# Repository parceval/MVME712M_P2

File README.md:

# MVME712M P2 Adapter Board

An open-source hardware replacement for the **Motorola MVME712M P2 Adapter**.

This board is designed to interface with Motorola VME CPU modules (such as the MVME147, MVME162, MVME167, and MVME177 series) to provide the necessary signals for the **MVME712M Transition Module**.

## Overview

The MVME712M P2 Adapter is a small passive board that plugs directly into the **P2 connector** on the VME backplane behind the CPU module. It breaks out the SCSI, Serial, and Centronics signals to a 50-pin header (or specific cable) that then connects to the MVME712M bulkhead/transition module.

This repository contains the KiCad design files to manufacture a modern replacement for the original Motorola part, which is often difficult to find or expensive on the used market.

## Hardware Features

* **Form Factor:** Standard VME P2 adapter dimensions.
* **Connectors:** * 96-pin DIN 41612 (Connector for VME P2 backplane).
* High-density or IDC headers for connection to the MVME712M transition board.

* **Compatibility:** Designed for use with Motorola MVME modules and the MVME712 series transition boards.
* **Passive Design:** No active components required; uses direct signal routing according to original Motorola specifications.

## Project Structure

```text
├── gerber/    # Gerbers, Drill files
└── docs/      # Pinout diagrams and reference manuals

```

## Compatibility List

This adapter is typically required for the following Motorola CPU boards when using an MVME712M transition module:

* MVME147
* MVME162 / MVME162P
* MVME167
* MVME172
* MVME177

## Usage

1. **Fabrication:** Use the provided Gerber files in the `Manufacturing/` folder to order PCBs (standard 1.6mm FR4, 1oz copper is sufficient).
2. **Assembly:** Solder the 96-pin DIN 41612 connector (Female/Socket) and the appropriate shrouded headers.
3. **Installation:** * Power down the VME chassis.
* Plug the adapter onto the **P2 pins** on the back of the backplane, directly behind your CPU module.
* Connect the internal ribbon cable from the adapter to your MVME712M transition module.

## License

This project is released under the [CERN Open Hardware Licence](https://cern-ohl.web.cern.ch/)

## Disclaimer

This is a community-driven project. While every effort has been made to ensure accuracy based on original documentation, use this hardware at your own risk. The author is not responsible for any damage to vintage VME equipment.

---

*Created by [parceval*](https://github.com/parceval)

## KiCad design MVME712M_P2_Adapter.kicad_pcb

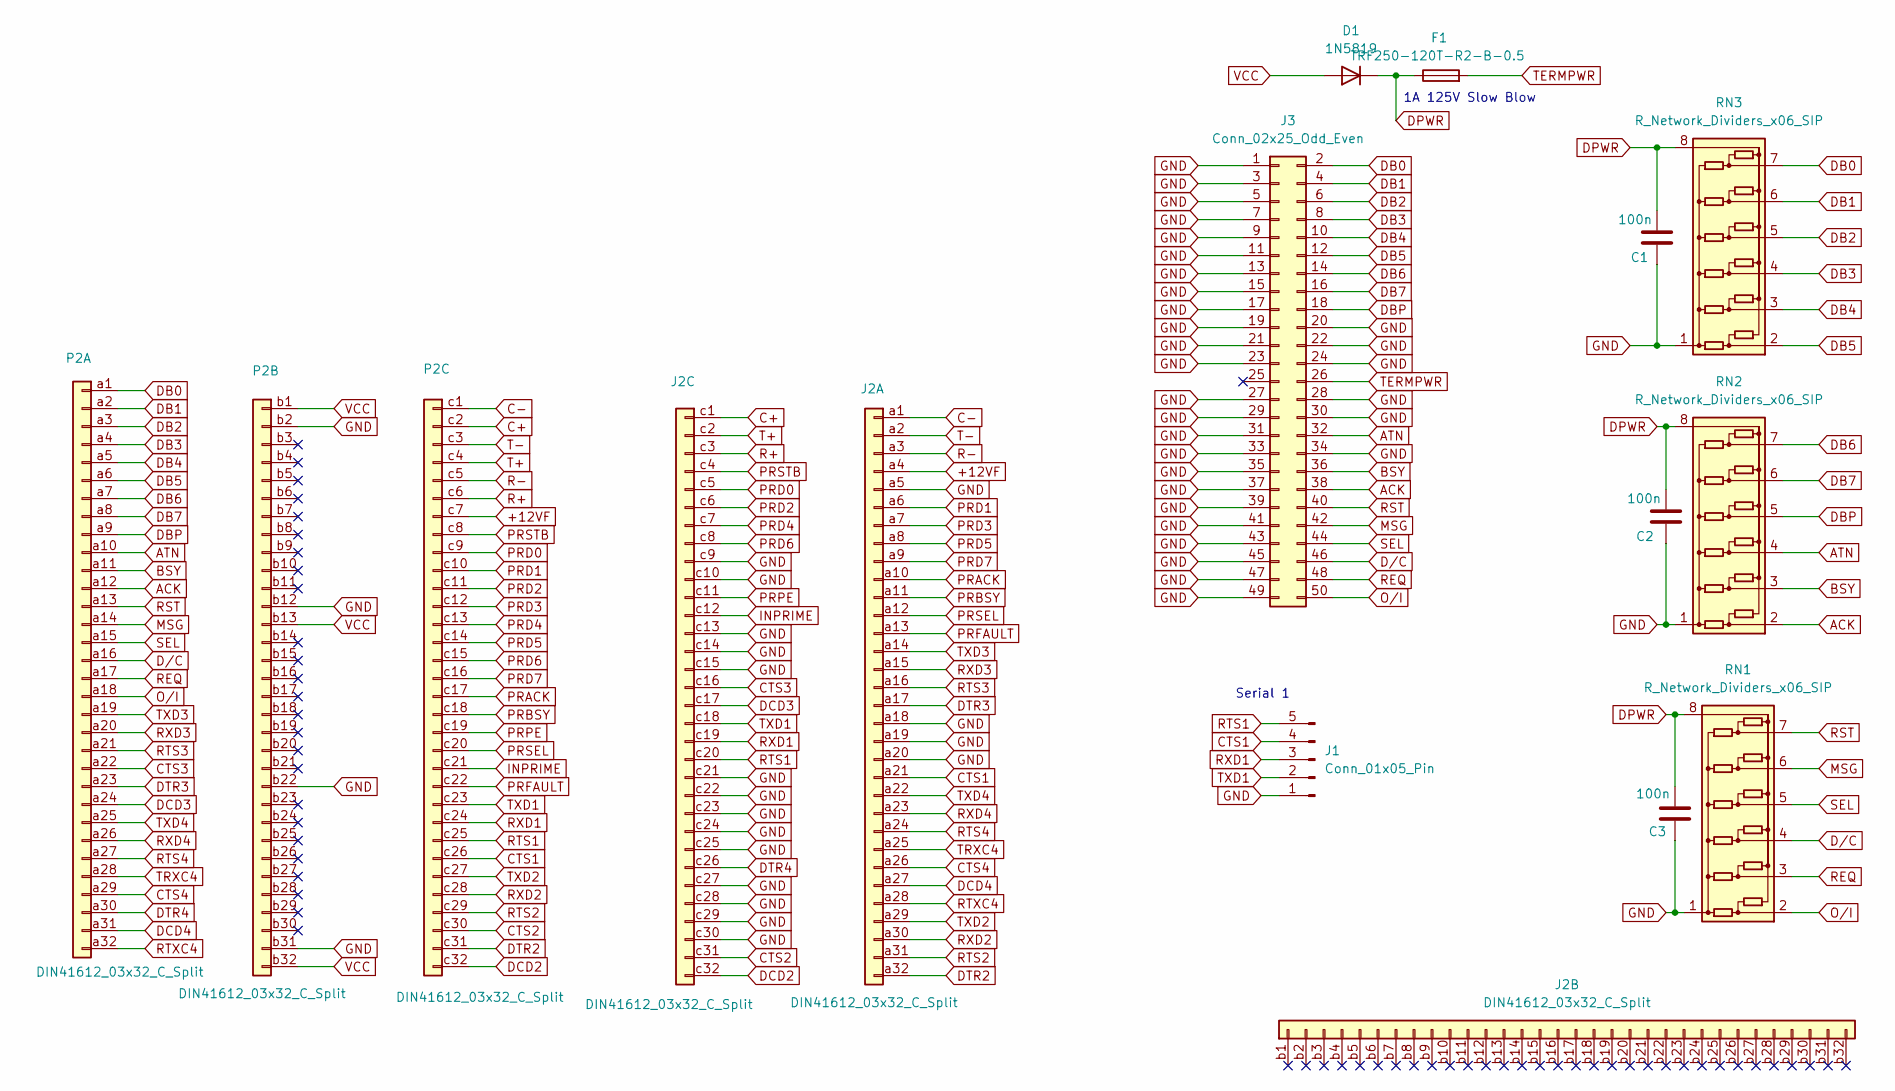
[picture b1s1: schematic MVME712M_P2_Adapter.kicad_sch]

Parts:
C1, C2, C3: 100n; C_Disc_D3.0mm_W1.6mm_P2.50mm
D1: 1N5819; D_DO-35_SOD27_P7.62mm_Horizontal
F1: TRF250-120T-R2-B-0.5; Fuse_Bourns_MF-RG500
J1: Conn_01x05_Pin; PinHeader_1x05_P2.54mm_Vertical
J2: DIN41612_03x32_C_Split; DIN41612_R_3x32_Male_Vertical_THT
J3: Conn_02x25_Odd_Even; IDC-Header_2x25_P2.54mm_Vertical
P2: DIN41612_03x32_C_Split; DIN41612_R_3x32_Female_Horizontal_THT
RN1, RN2, RN3: R_Network_Dividers_x06_SIP; R_Array_SIP8

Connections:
+12VF: J2.a4, P2.c7
ACK: J3.38, P2.a12, RN2.2 (R1)
ATN: J3.32, P2.a10, RN2.4 (R3)
BSY: J3.36, P2.a11, RN2.3 (R2)
C+: J2.c1, P2.c2
C-: J2.a1, P2.c1
CTS1: J1.4, J2.a21, P2.c26
CTS2: J2.c31, P2.c30
CTS3: J2.c16, P2.a22
CTS4: J2.a26, P2.a29
DB0: J3.2, P2.a1, RN3.7 (R6)
DB1: J3.4, P2.a2, RN3.6 (R5)
DB2: J3.6, P2.a3, RN3.5 (R4)
DB3: J3.8, P2.a4, RN3.4 (R3)
DB4: J3.10, P2.a5, RN3.3 (R2)
DB5: J3.12, P2.a6, RN3.2 (R1)
DB6: J3.14, P2.a7, RN2.7 (R6)
DB7: J3.16, P2.a8, RN2.6 (R5)
DBP: J3.18, P2.a9, RN2.5 (R4)
DCD2: J2.c32, P2.c32
DCD3: J2.c17, P2.a24
DCD4: J2.a27, P2.a31
DPWR: C1.1, C2.1, C3.1, D1.1 (K), F1.1, RN1.8 (COM2), RN2.8 (COM2), RN3.8 (COM2)
DTR2: J2.a32, P2.c31
DTR3: J2.a17, P2.a23
DTR4: J2.c26, P2.a30
D/C: J3.46, P2.a16, RN1.4 (R3)
GND: C1.2, C2.2, C3.2, J1.1, J2.a5, J2.a18, J2.a19, J2.a20, J2.c9, J2.c10, J2.c13, J2.c14, J2.c15, J2.c21, J2.c22, J2.c23, J2.c24, J2.c25, J2.c27, J2.c28, J2.c29, J2.c30, J3.1, J3.3, J3.5, J3.7, J3.9, J3.11, J3.13, J3.15, J3.17, J3.19, J3.20, J3.21, J3.22, J3.23, J3.24, J3.27, J3.28, J3.29, J3.30, J3.31, J3.33, J3.34, J3.35, J3.37, J3.39, J3.41, J3.43, J3.45, J3.47, J3.49, P2.b2, P2.b12, P2.b22, P2.b31, RN1.1 (COM1), RN2.1 (COM1), RN3.1 (COM1)
INPRIME: J2.c12, P2.c21
MSG: J3.42, P2.a14, RN1.6 (R5)
O/I: J3.50, P2.a18, RN1.2 (R1)
PRACK: J2.a10, P2.c17
PRBSY: J2.a11, P2.c18
PRD0: J2.c5, P2.c9
PRD1: J2.a6, P2.c10
PRD2: J2.c6, P2.c11
PRD3: J2.a7, P2.c12
PRD4: J2.c7, P2.c13
PRD5: J2.a8, P2.c14
PRD6: J2.c8, P2.c15
PRD7: J2.a9, P2.c16
PRFAULT: J2.a13, P2.c22
PRPE: J2.c11, P2.c19
PRSEL: J2.a12, P2.c20
PRSTB: J2.c4, P2.c8
R+: J2.c3, P2.c6
R-: J2.a3, P2.c5
REQ: J3.48, P2.a17, RN1.3 (R2)
RST: J3.40, P2.a13, RN1.7 (R6)
RTS1: J1.5, J2.c20, P2.c25
RTS2: J2.a31, P2.c29
RTS3: J2.a16, P2.a21
RTS4: J2.a24, P2.a27
RTXC4: J2.a28, P2.a32
RXD1: J1.3, J2.c19, P2.c24
RXD2: J2.a30, P2.c28
RXD3: J2.a15, P2.a20
RXD4: J2.a23, P2.a26
SEL: J3.44, P2.a15, RN1.5 (R4)
T+: J2.c2, P2.c4
T-: J2.a2, P2.c3
TERMPWR: F1.2, J3.26
TRXC4: J2.a25, P2.a28
TXD1: J1.2, J2.c18, P2.c23
TXD2: J2.a29, P2.c27
TXD3: J2.a14, P2.a19
TXD4: J2.a22, P2.a25
VCC: D1.2 (A), P2.b1, P2.b13, P2.b32

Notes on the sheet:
1A 125V Slow Blow
Serial 1

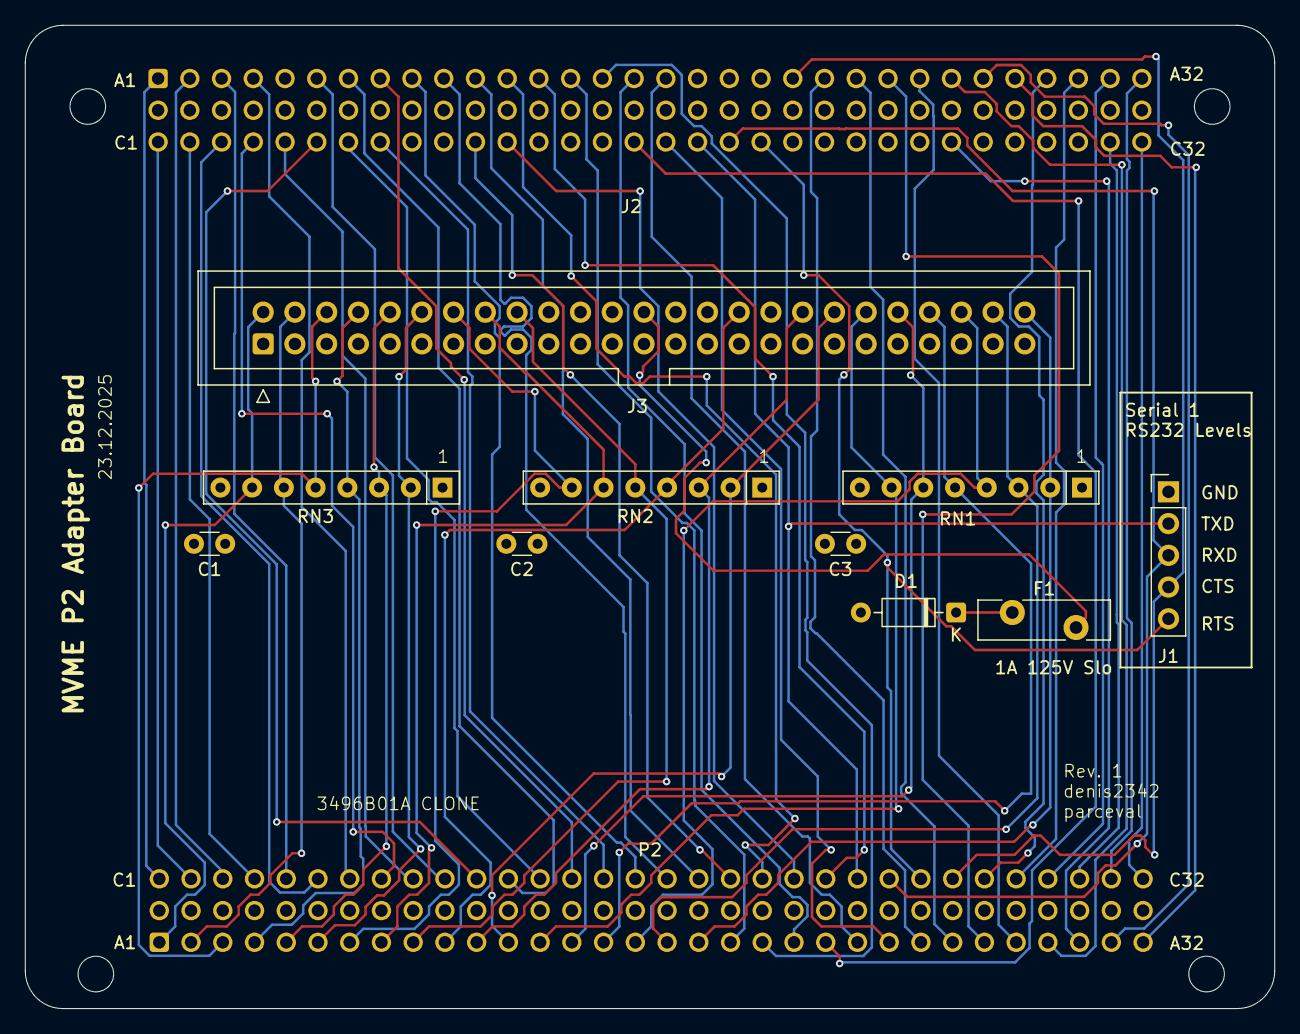
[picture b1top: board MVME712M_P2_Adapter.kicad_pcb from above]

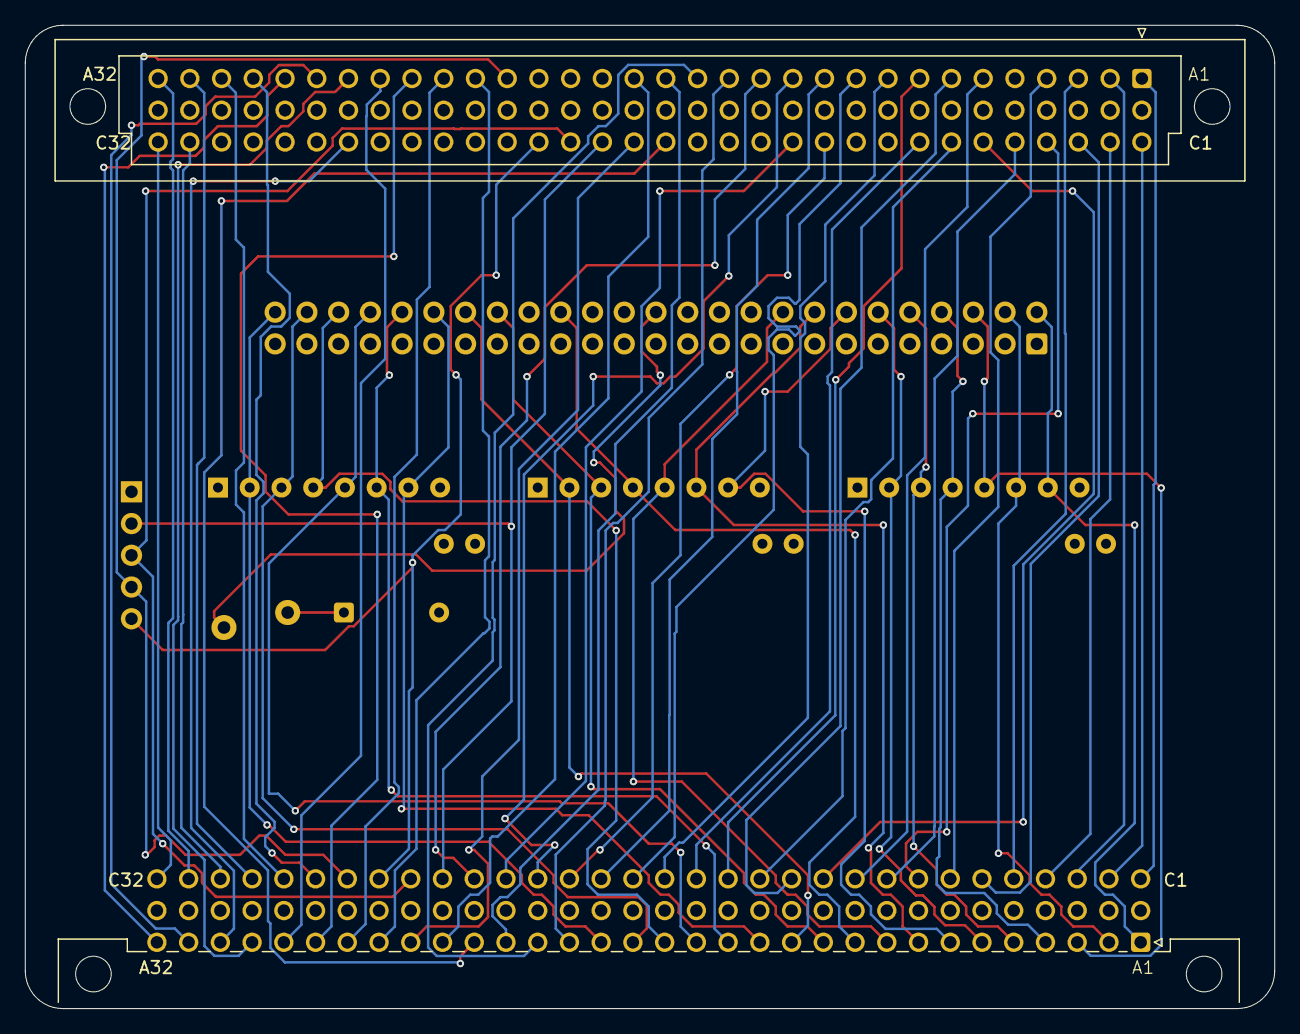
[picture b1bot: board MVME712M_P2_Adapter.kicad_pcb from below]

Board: 4 copper layers, 100.0 x 78.7 mm, 12 parts (2 on the bottom side), 68 nets.

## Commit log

2025-12-23 added RS232 text
2025-12-23 added RS232 text on pcb
2025-12-23 readme
2025-12-24 added license file and cleanup
